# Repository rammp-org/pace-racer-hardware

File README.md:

# PACE Racer motor controller (KiCad hardware)
Welcome to the official hardware repository for the **PACE V0 (RACER)** motor controller board. This repository contains all KiCad design schematics, layout files, and hardware documentation required to manufacture, test, and interface with the RACER platform. 
The companion firmware for this board is under active development in the companion repository: `pace-racer-firmware`.

**How this repo works:** humans commit KiCad sources; CI (KiBot) runs ERC and DRC on every PR and builds gerbers, BOM, position, ibom, PDFs, STEP and renders. Tagging `VnRm` publishes those as a GitHub Release. See `docs/style-guide.md` for conventions and `docs/decisions/` for the why behind unusual choices.
<div align="center">

## Documentation & Resources
### Access the [schematics and an interactive board viewer here!](https://kicanvas.org/?repo=https%3A%2F%2Fgithub.com%2Frammp-org%2Fpace-racer-hardware%2Ftree%2Fmain%2Fpace-core)

---

<div align="left">

## Hardware Architecture Overview

The PACE V0 (RACER) is a high-performance, intelligent 3-phase inverter platform powered by an ESP32-S3. It is engineered to support both high-frequency **Field-Oriented Control (FOC)** and traditional **Trapezoidal (Block) Commutation** strategies. 

``` mermaid
flowchart TD
    %% Upstream USB Environment
    subgraph Upstream ["Upstream Side (Isolated USB Environment)"]
        USB["USB-C Connector<br>(USB1)"] -->|VBUS / GND_USB| VUSB["+5V-USB Rail<br>& GND-USB Rail"]
        VUSB -->|Powers Upstream Side| ISO_In["ADUM3160 Digital Isolator<br>(U4 Upstream Pins)"]
    end

    %% Galvanic Isolation Barrier
    subgraph Barrier ["Galvanic Isolation Boundary"]
        ISO_In -.->|Optical/Magnetic Data Isolation| ISO_Out["ADUM3160 Digital Isolator<br>(U4 Downstream Pins)"]
        SW3{"SW3 Switch<br>(DPDT)"}
    end

    %% High Voltage Input Power Stage
    subgraph HV_Stage ["High-Voltage Input Power Stage"]
        BATT["+BATT Input Rail<br>(48V Nominal Target)"] --> Caps["DC-Link Capacitor Buffers<br>(100V Continuous Rating Limit)"]
        Caps --> XLBuck["XL7015E1 Buck Converter<br>(U6 Stage)"]
    end

    %% Main Logic Subsystems
    subgraph Logic_Rails ["Downstream Logic & Control Subsystem"]
        XLBuck -->|Step Down| V5["+5V Local Rail"]
        
        V5 -->|Linear Regulation| AMS["AMS1117-3.3 LDO (U5)"]
        AMS -->|Logic Power| V33["+3V3 Main MCU Rail"]
        
        V5 -->|Precision Division| REF["REF35160 Reference IC (U7)"]
        REF -->|ADC Baseline Shift| V16["1V6-REF Precision Rail"]
        
        V33 -->|Powers MCU| MCU["ESP32-S3 Processing Core<br>(System GND)"]
        V16 -->|Shunt Offset Bias| MCU
        ISO_Out -->|Isolated USB Signals| MCU
    end

    %% Isolation Mode Controls
    VUSB -->|Route Bus Voltage| SW3
    SW3 -->|Flipped State: Breaks Ground Loops| Logic_Rails
```

### 1. Processing & Inverter Stage
* **Core MCU**: An ESP32-S3-WROOM-1 module handles raw motor control mathematics, wireless telemetry, and hardware interrupt management.
* **Gate Driver**: A TI DRV8353SRTAT 3-phase gate driver provides independent high-side/low-side drive configurations, hardware fault line triggers, and runtime register adjustments via SPI.
* **Power MOSFETs**: 6x ISC0802NLSATMA1 MOSFETs are structured in a traditional 3-phase half-bridge bridge array.
* **Current Sensing**: Dual-purpose inline, low-side 1.0 mΩ current sense shunts (`R1`, `R2`, `R3`) are deployed on all three phases to capture fast current waveforms for precision FOC.

### 2. Sensor Framework
* **Rotor Position Feedback**: Supports dual encoder paradigms:
  * High-speed SPI telemetry via the MT6701 Magnetic Rotary Encoder interface.
  * Discrete input lines for standard 3-phase Hall effect sensor elements (`hall-a`, `hall-b`, `hall-c`).
* **Thermal Management**: 4x LM75ADP I2C digital temperature monitors are distributed across key thermal zones on a single I2C bus. Fixed hardware addressing assigns them respectively to `0x4C`, `0x4D`, `0x4E`, and `0x4F`.

### 3. Communications & Safety
* **Wired Networking**: A Wiznet W5500 Ethernet Coprocessor configuration allows stable, high-throughput network communication over a shared high-speed SPI bus.
* **Galvanic Isolation**: The upstream USB-C debugging connection features an ADUM3160BRWZ-RL digital isolation chip to safely separate logic lines from high-voltage battery transient grounds (see `docs/decisions/0001-ground-domains.md`) during live tuning.

---

## Hardware Pin Mapping Reference

This table is generated from the schematic netlist by `tools/gen_readme.py` and checked in CI. Do not edit it by hand.
Net names follow `docs/style-guide.md` (lowercase domain-kebab); the firmware `hal_pins.h` should use these names.

<!-- BEGIN GENERATED: pinmap -->
| MCU pin | Net | Connected to |
| :-- | :-- | :-- |
| IO0/st-boot (pin 27) | `mcu-boot` | R8, SW1 |
| RXD0 (pin 36) | `uart-rx` | J4 |
| TXD0 (pin 37) | `uart-tx` | J4 |
| IO1/adc1-0 (pin 39) | `vref-1v6` | C23, C27, TP24, U2, U7 |
| IO2/adc1-1 (pin 38) | `mcu-io2` | J4 |
| IO3/st-jtag/adc1-2 (pin 15) | `hall-a` | C42, R34 |
| IO4/adc1-3 (pin 4) | `isense-a` | C30, R10 |
| IO5/adc1-4 (pin 5) | `isense-b` | C29, R21 |
| IO6/adc1-5 (pin 6) | `isense-c` | C28, R22 |
| IO7/adc1-6 (pin 7) | `pwm-c-low` | R26, U2 |
| IO8/adc1-7 (pin 12) | `pwm-a-high` | R31, U2 |
| IO9/adc1-8 (pin 17) | `hall-c` | C40, R25 |
| IO10/adc1-9/FSPI-CS (pin 18) | `eth-spi-cs` | J2, R23 |
| IO11/FSPI-D (pin 19) | `spi-copi` | J2, U2 |
| IO12/FSPI-CLK (pin 20) | `spi-clk` | J2, U2 |
| IO13/FSPI-Q (pin 21) | `spi-cipo` | J2, R17, U2 |
| IO14 (pin 22) | `eth-irq` | J2 |
| IO15 (pin 8) | `pwm-c-high` | R27, U2 |
| IO16 (pin 9) | `pwm-b-low` | R28, U2 |
| IO17 (pin 10) | `pwm-b-high` | R29, U2 |
| IO18 (pin 11) | `pwm-a-low` | R30, U2 |
| IO19/USBD- (pin 13) | `usb-dm` | U4 |
| IO20/USBD+ (pin 14) | `usb-dp` | U4 |
| IO21 (pin 23) | `eth-reset` | J2 |
| IO35 (pin 28) | `enc-spi-cipo` | U12 |
| IO36 (pin 29) | `enc-spi-copi` | J4, U12 |
| IO37 (pin 30) | `enc-spi-clk` | U12 |
| IO38 (pin 31) | `enc-spi-cs` | R24, U12 |
| IO39 (pin 32) | `drv-spi-cs` | U2 |
| IO40 (pin 33) | `drv-fault` | R16, U2 |
| IO41 (pin 34) | `led-green` | D2, J4 |
| IO42 (pin 35) | `led-blue` | D1, J4 |
| IO45/st-spi-v (pin 26) | `i2c-sda` | J4, R39, U10, U11, U8, U9 |
| IO46/st-rom (pin 16) | `hall-b` | C41, R33 |
| IO47 (pin 24) | `drv-enable` | R32, U2 |
| IO48 (pin 25) | `i2c-scl` | J4, R40, U10, U11, U8, U9 |
| EN (pin 3) | `mcu-reset` | R9, SW2 |
<!-- END GENERATED: pinmap -->

---

## Power Distribution & Topology

The RACER PCB layout handles standard heavy industrial current loops alongside sensitive logic rails. Care must be taken during low-level development to understand the distinct ground rules and supply behavior.

* **Main DC Power Stage Input (`+BATT`)**: Accepts high-voltage input up to 60V DC. High and low-frequency buffer capacitor banks are placed immediately across each half-bridge phase to suppress heavy inductive switching ripples up to 25MHz.
* **Logic Subsystem Buck (5V Rail)**: Driven by an XL7015E1 high-voltage buck regulator topology, dropping the high-voltage input down to a common local 5V line.
* **Microcontroller Supply (3.3V Rail)**: An AMS1117-3.3 linear regulator drops the local 5V line to a stable 3.3V rail dedicated to powering the ESP32-S3 and onboard sensors.
* **Analog Ingestion Bias Reference (`vref-1v6`)**: Formed via a REF35160QDBVR high-precision reference generator connected to the 5V line. This outputs a fixed 1.6V reference bias to calibrate the inline current shunt amplifiers, permitting measurement of negative and positive phase currents across the full bi-directional stroke.
* **Isolation Boundary Notice**: The 5V-USB rail is strictly limited to powering the upstream digital isolator components. Flipping the physical isolation switch (`SW3`) cleanly detaches the target ground (`GND`) from development computer USB shields (`GND-USB`) to protect computer infrastructure against high-power faults.

---

## First-Stage Firmware Initialization Blueprint

To quickly bring up prototype firmware on `pace-racer-firmware`, organize your driver initializations using this execution checklist:

### Phase 1: Core Systems & Diagnostic Telemetry
1. Define the physical I/O allocations outlined in the pin reference table.
2. Initialize diagnostic LEDs (`IO41`, `IO42`) to indicate a booting state.
3. Fire up the shared I2C bus over `IO45` and `IO48` to loop and register responses from the four LM75ADP temperature sensor configurations at addresses `0x4C` through `0x4F`. 

### Phase 2: Inverter Protection & Commutation Interfaces
1. Configure `IO40` (`drv-fault`) as an active-low hardware interrupt line. Ensure its handler instantly forces all PWM generation lines into a low (disabled) safety state if triggered.
2. Initialize the main SPI communications bus over pins `spi-copi`, `spi-clk`, and `spi-cipo`. Pull the gate driver chip select (`IO39`) low to configure the DRV8353 operational state registers.
3. For **Field-Oriented Control (FOC)**, configure high-speed SPI capture over the encoder subsystem (`IO35`, `IO37`, `IO38`) to decode magnetic orientation data from the MT6701.
4. For **Trapezoidal Commutation**, establish change-of-state interrupt routines tracking discrete pin changes across Hall effect inputs (`IO3`, `IO46`, `IO9`).

### Phase 3: Ethernet Networking
1. Cycle the hardware reset pin `IO21` to clear the internal registers of the W5500 Ethernet chip.
2. Configure SPI tracking over the controller chip select pin `IO10`.
3. Initialize the raw sockets over network stacks using the standard `eth-irq` (`IO14`) interrupt pin to manage incoming and outgoing network interface events without blocking the high-frequency motor control loops.

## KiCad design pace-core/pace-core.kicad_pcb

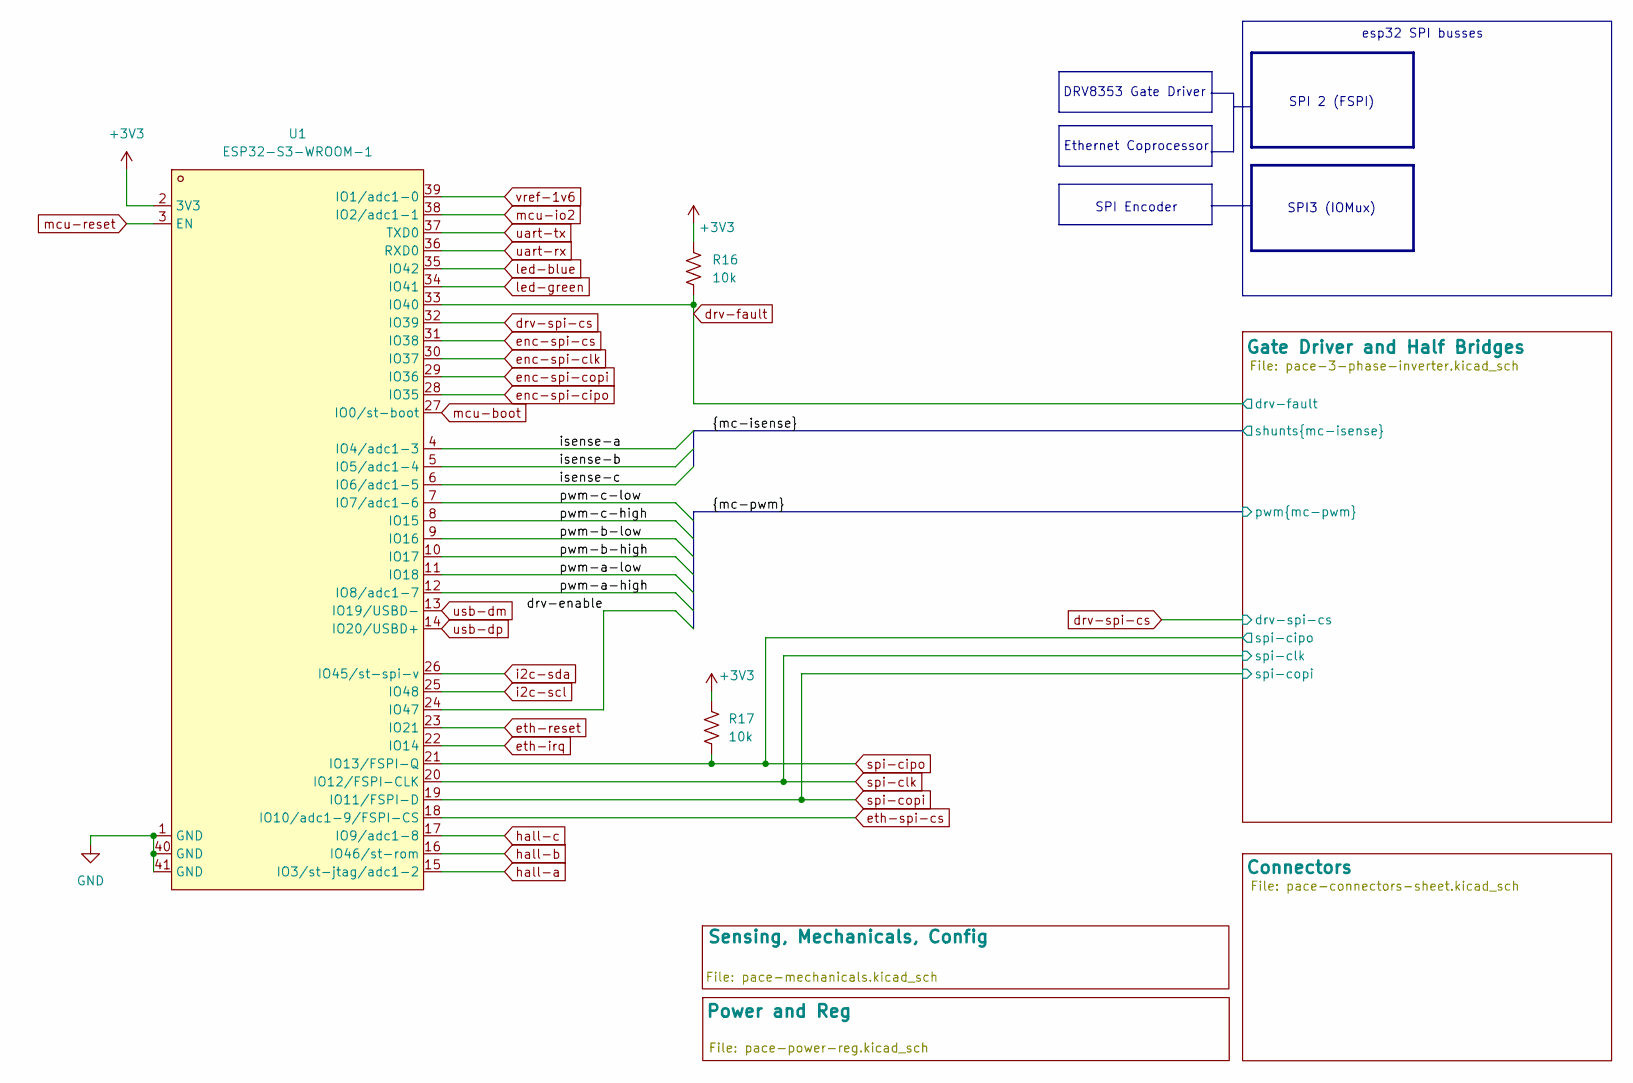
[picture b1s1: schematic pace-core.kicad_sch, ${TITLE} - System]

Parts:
R16, R17: 10k; R_0402_1005Metric
U1: ESP32-S3-WROOM-1; WIRELM-SMD_ESP32-S3-WROOM-1; MPN ESP32-S3-WROOM-1-N16R2; LCSC Part C2913205

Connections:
+3V3: R16.1, R17.1, U1.2 (3V3); also elsewhere on the board
/drv-enable: U1.24 (IO47); also elsewhere on the board
/isense-a: U1.4 (IO4/adc1-3); also elsewhere on the board
/isense-b: U1.5 (IO5/adc1-4); also elsewhere on the board
/isense-c: U1.6 (IO6/adc1-5); also elsewhere on the board
/pwm-a-high: U1.12 (IO8/adc1-7); also elsewhere on the board
/pwm-a-low: U1.11 (IO18); also elsewhere on the board
/pwm-b-high: U1.10 (IO17); also elsewhere on the board
/pwm-b-low: U1.9 (IO16); also elsewhere on the board
/pwm-c-high: U1.8 (IO15); also elsewhere on the board
/pwm-c-low: U1.7 (IO7/adc1-6); also elsewhere on the board
GND: U1.1 (GND), U1.40 (GND), U1.41 (GND); also elsewhere on the board
drv-fault: R16.2, U1.33 (IO40); also elsewhere on the board
drv-spi-cs: U1.32 (IO39); also elsewhere on the board
enc-spi-cipo: U1.28 (IO35); also elsewhere on the board
enc-spi-clk: U1.30 (IO37); also elsewhere on the board
enc-spi-copi: U1.29 (IO36); also elsewhere on the board
enc-spi-cs: U1.31 (IO38); also elsewhere on the board
eth-irq: U1.22 (IO14); also elsewhere on the board
eth-reset: U1.23 (IO21); also elsewhere on the board
eth-spi-cs: U1.18 (IO10/adc1-9/FSPI-CS); also elsewhere on the board
hall-a: U1.15 (IO3/st-jtag/adc1-2); also elsewhere on the board
hall-b: U1.16 (IO46/st-rom); also elsewhere on the board
hall-c: U1.17 (IO9/adc1-8); also elsewhere on the board
i2c-scl: U1.25 (IO48); also elsewhere on the board
i2c-sda: U1.26 (IO45/st-spi-v); also elsewhere on the board
led-blue: U1.35 (IO42); also elsewhere on the board
led-green: U1.34 (IO41); also elsewhere on the board
mcu-boot: U1.27 (IO0/st-boot); also elsewhere on the board
mcu-io2: U1.38 (IO2/adc1-1); also elsewhere on the board
mcu-reset: U1.3 (EN); also elsewhere on the board
spi-cipo: R17.2, U1.21 (IO13/FSPI-Q); also elsewhere on the board
spi-clk: U1.20 (IO12/FSPI-CLK); also elsewhere on the board
spi-copi: U1.19 (IO11/FSPI-D); also elsewhere on the board
uart-rx: U1.36 (RXD0); also elsewhere on the board
uart-tx: U1.37 (TXD0); also elsewhere on the board
usb-dm: U1.13 (IO19/USBD-); also elsewhere on the board
usb-dp: U1.14 (IO20/USBD+); also elsewhere on the board

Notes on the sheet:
SPI3 (IOMux)
SPI 2 (FSPI)
SPI Encoder
Ethernet Coprocessor
DRV8353 Gate Driver
esp32 SPI busses

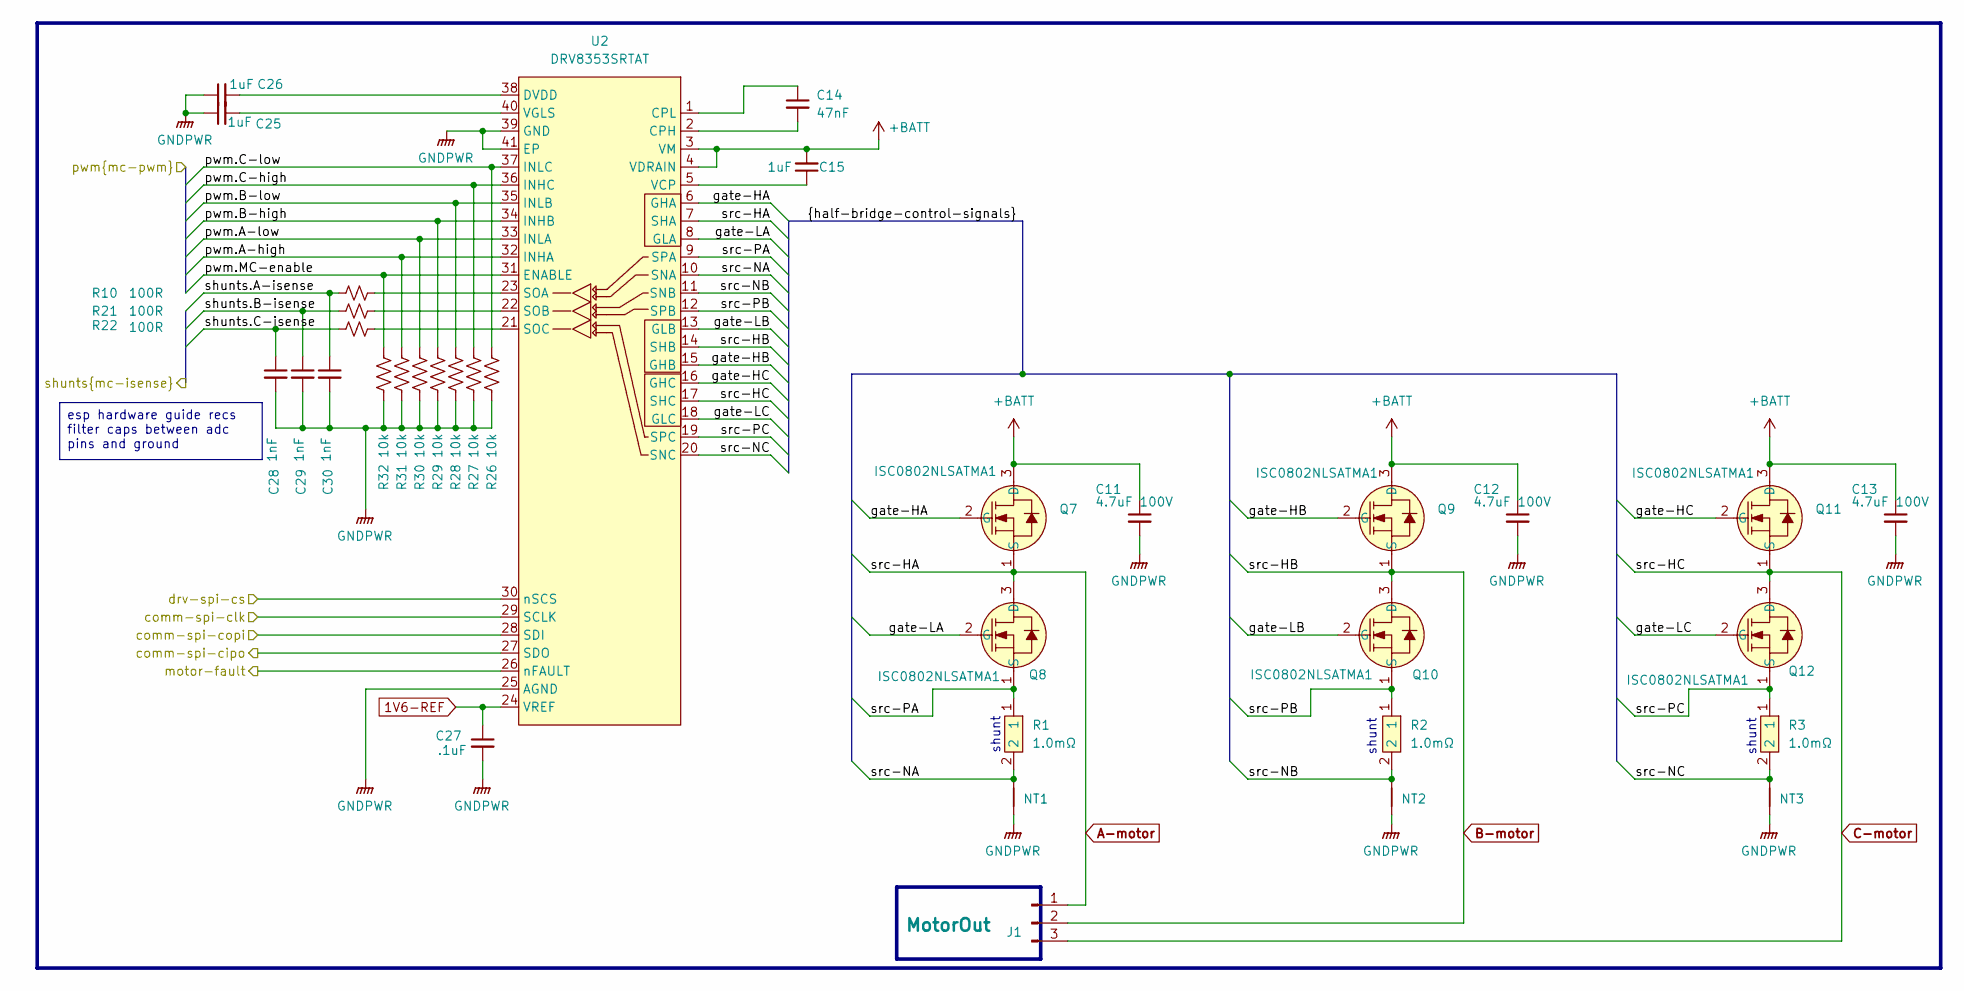
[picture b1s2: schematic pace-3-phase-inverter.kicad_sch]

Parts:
C11, C12, C13: 4.7uF 100V; C_1210_3225Metric
C14: 47nF; C_0603_1608Metric
C15, C25, C26: 1uF; C_1206_3216Metric
C27: .1uF; C_0402_1005Metric
C28, C29, C30: 1nF; C_0402_1005Metric
J1: MotorOut; 3PhaseMotorPigtail
NT1, NT2, NT3: NetTie_2; shunt-net-tie
Q7, Q8, Q9, Q10, Q11, Q12: ISC0802NLSATMA1; PG-TDSON-8_L5.9-W5.1-P1.27-LS6.1-BL; MPN ISC0802NLSATMA1; LCSC Part C3288904
R1, R2, R3: 1.0mΩ; RES-SMD_L6.3-W3.1-1; MPN DSLR-M-3-1F; LCSC Part C41382682
R10, R21, R22: 100R; R_0402_1005Metric
R26, R27, R28, R29, R30, R31, R32: 10k; R_0402_1005Metric
U2: DRV8353SRTAT; WQFN-40_L6.0-W6.0-P0.50-TL-EP4.2; MPN DRV8353SRTAT; LCSC Part C2150480

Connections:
+BATT: C11.1, C12.1, C13.1, C15.2, Q7.3 (D), Q9.3 (D), Q11.3 (D), U2.3 (VM), U2.4 (VDRAIN); also elsewhere on the board
/Gate Driver and Half Bridges/gate-a-high: Q7.2 (G), U2.6 (GHA)
/Gate Driver and Half Bridges/gate-a-low: Q8.2 (G), U2.8 (GLA)
/Gate Driver and Half Bridges/gate-b-high: Q9.2 (G), U2.15 (GHB)
/Gate Driver and Half Bridges/gate-b-low: Q10.2 (G), U2.13 (GLB)
/Gate Driver and Half Bridges/gate-c-high: Q11.2 (G), U2.16 (GHC)
/Gate Driver and Half Bridges/gate-c-low: Q12.2 (G), U2.18 (GLC)
/Gate Driver and Half Bridges/shunt-a-n: NT1.2, R1.2, U2.10 (SNA)
/Gate Driver and Half Bridges/shunt-a-p: Q8.1 (S), R1.1, U2.9 (SPA)
/Gate Driver and Half Bridges/shunt-b-n: NT2.2, R2.2, U2.11 (SNB)
/Gate Driver and Half Bridges/shunt-b-p: Q10.1 (S), R2.1, U2.12 (SPB)
/Gate Driver and Half Bridges/shunt-c-n: NT3.2, R3.2, U2.20 (SNC)
/Gate Driver and Half Bridges/shunt-c-p: Q12.1 (S), R3.1, U2.19 (SPC)
/drv-enable: R32.2, U2.31 (ENABLE); also elsewhere on the board
/isense-a: C30.1, R10.1; also elsewhere on the board
/isense-b: C29.1, R21.1; also elsewhere on the board
/isense-c: C28.1, R22.1; also elsewhere on the board
/pwm-a-high: R31.2, U2.32 (INHA); also elsewhere on the board
/pwm-a-low: R30.2, U2.33 (INLA); also elsewhere on the board
/pwm-b-high: R29.2, U2.34 (INHB); also elsewhere on the board
/pwm-b-low: R28.2, U2.35 (INLB); also elsewhere on the board
/pwm-c-high: R27.2, U2.36 (INHC); also elsewhere on the board
/pwm-c-low: R26.2, U2.37 (INLC); also elsewhere on the board
GND: C11.2, C12.2, C13.2, C25.1, C26.1, C27.2, C28.2, C29.2, C30.2, NT1.1, NT2.1, NT3.1, R26.1, R27.1, R28.1, R29.1, R30.1, R31.1, R32.1, U2.25 (AGND), U2.39 (GND), U2.41 (EP); also elsewhere on the board
unnamed: C14.2, U2.2 (CPH)
unnamed: C14.1, U2.1 (CPL)
unnamed: C26.2, U2.38 (DVDD)
unnamed: R10.2, U2.23 (SOA)
unnamed: R21.2, U2.22 (SOB)
unnamed: R22.2, U2.21 (SOC)
unnamed: C15.1, U2.5 (VCP)
unnamed: C25.2, U2.40 (VGLS)
drv-fault: U2.26 (nFAULT); also elsewhere on the board
drv-spi-cs: U2.30 (nSCS); also elsewhere on the board
mot-a: J1.1, Q7.1 (S), Q8.3 (D), U2.7 (SHA)
mot-b: J1.2, Q9.1 (S), Q10.3 (D), U2.14 (SHB)
mot-c: J1.3, Q11.1 (S), Q12.3 (D), U2.17 (SHC)
spi-cipo: U2.27 (SDO); also elsewhere on the board
spi-clk: U2.29 (SCLK); also elsewhere on the board
spi-copi: U2.28 (SDI); also elsewhere on the board

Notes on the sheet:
shunt
esp hardware guide recs filter caps between adc pins and ground

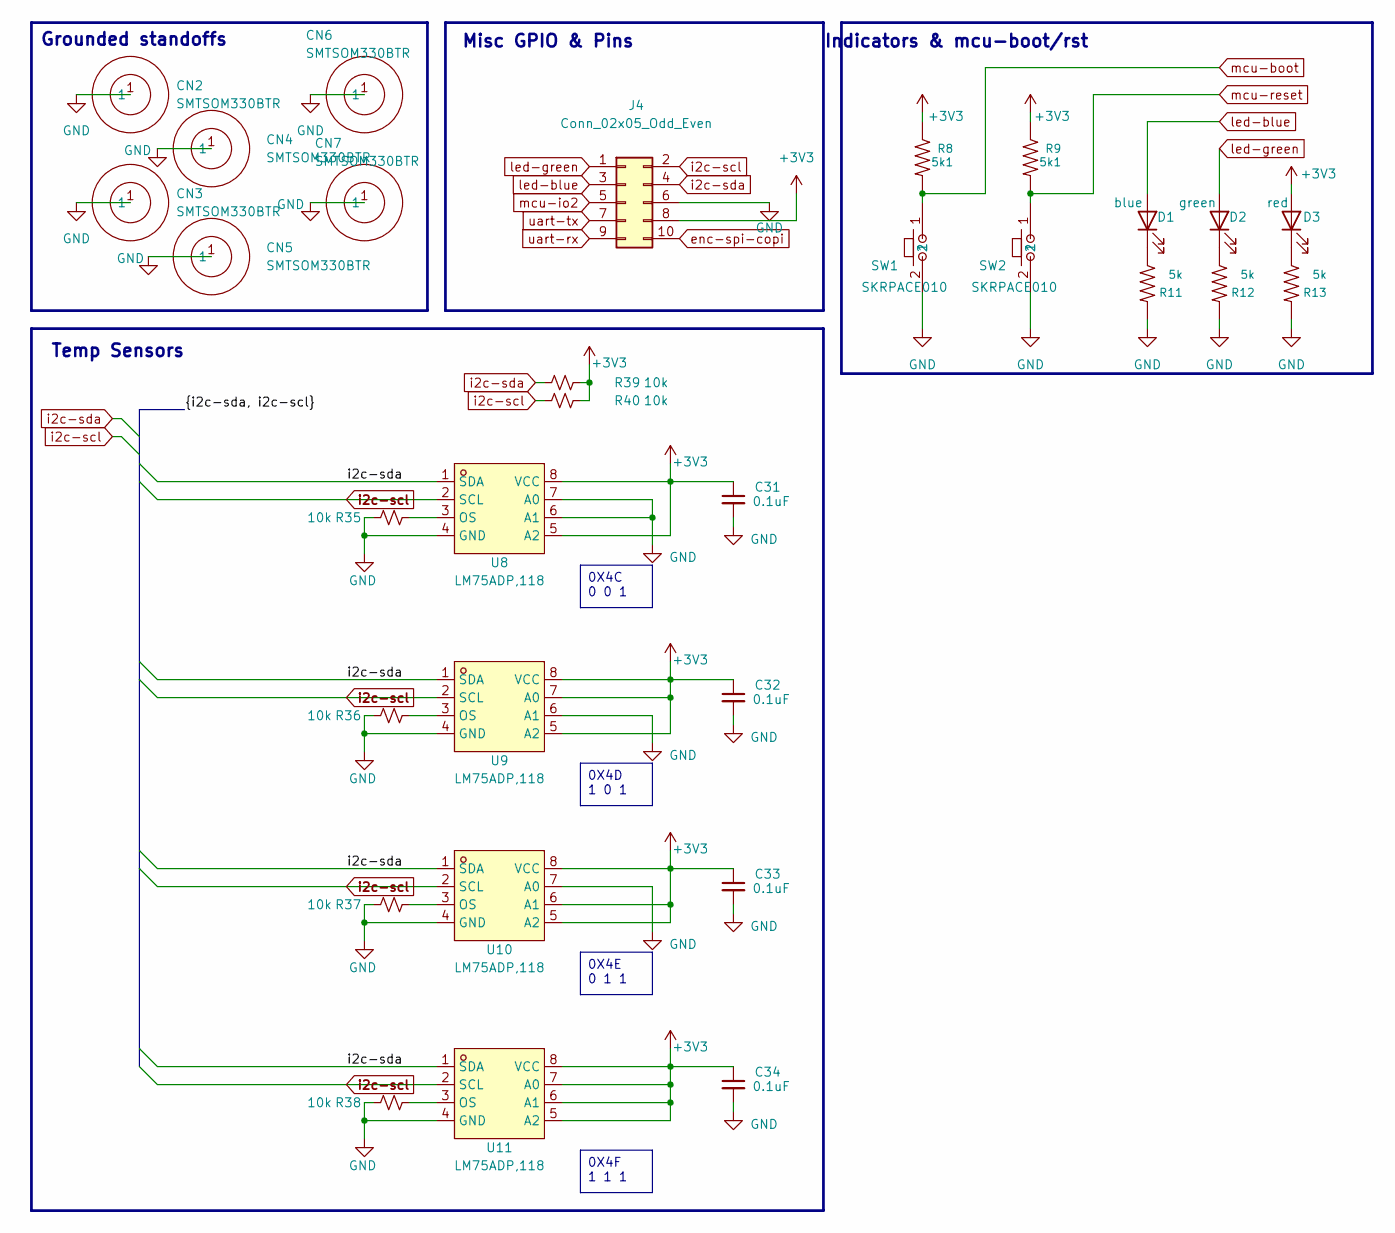
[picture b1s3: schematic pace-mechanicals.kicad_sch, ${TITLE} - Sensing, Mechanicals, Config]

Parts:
C31, C32, C33, C34: 0.1uF; C_0402_1005Metric
CN2, CN3, CN4, CN5, CN6, CN7: SMTSOM330BTR; M3-TH_BD6.0-D4.3; MPN SMTSOM330BTR; LCSC Part C5221843
D1: blue; LED_0805_2012Metric; LCSC_Part_Number C84259
D2: green; LED_0805_2012Metric; LCSC_Part_Number C84260
D3: red; LED_0805_2012Metric; LCSC_Part_Number C84256
J4: Conn_02x05_Odd_Even; PinHeader_2x05_P2.54mm_Vertical_SMD
R8, R9: 5k1; R_0402_1005Metric; LCSC_Part_Number C25905
R11, R12, R13: 5k; R_0402_1005Metric; LCSC_Part_Number C11702
R35, R36, R37, R38, R39, R40: 10k; R_0402_1005Metric
SW1, SW2: SKRPACE010; KEY-SMD_4P-L4.2-W3.2-P2.20-LS4.6; MPN SKRPACE010; LCSC Part C139797
U8, U9, U10, U11: LM75ADP,118; TSSOP-8_L3.0-W3.0-P0.65-LS4.9-BL; MPN LM75ADP,118; LCSC Part C843694

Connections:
+3V3: C31.1, C32.1, C33.1, C34.1, D3.2 (A), J4.8, R8.1, R9.1, R39.2, R40.2, U8.5 (A2), U8.8 (VCC), U9.5 (A2), U9.7 (A0), U9.8 (VCC), U10.5 (A2), U10.6 (A1), U10.8 (VCC), U11.5 (A2), U11.6 (A1), U11.7 (A0), U11.8 (VCC); also elsewhere on the board
GND: C31.2, C32.2, C33.2, C34.2, CN2.1 (1_1), CN3.1 (1_1), CN4.1 (1_1), CN5.1 (1_1), CN6.1 (1_1), CN7.1 (1_1), J4.6, R11.2, R12.2, R13.2, R35.2, R36.2, R37.2, R38.2, SW1.2, SW2.2, U8.4 (GND), U8.6 (A1), U8.7 (A0), U9.4 (GND), U9.6 (A1), U10.4 (GND), U10.7 (A0), U11.4 (GND); also elsewhere on the board
unnamed: D1.1 (K), R11.1
unnamed: D2.1 (K), R12.1
unnamed: D3.1 (K), R13.1
unnamed: R35.1, U8.3 (OS)
unnamed: R36.1, U9.3 (OS)
unnamed: R37.1, U10.3 (OS)
unnamed: R38.1, U11.3 (OS)
enc-spi-copi: J4.10; also elsewhere on the board
i2c-scl: J4.2, R40.1, U8.2 (SCL), U9.2 (SCL), U10.2 (SCL), U11.2 (SCL); also elsewhere on the board
i2c-sda: J4.4, R39.1, U8.1 (SDA), U9.1 (SDA), U10.1 (SDA), U11.1 (SDA); also elsewhere on the board
led-blue: D1.2 (A), J4.3; also elsewhere on the board
led-green: D2.2 (A), J4.1; also elsewhere on the board
mcu-boot: R8.2, SW1.1; also elsewhere on the board
mcu-io2: J4.5; also elsewhere on the board
mcu-reset: R9.2, SW2.1; also elsewhere on the board
uart-rx: J4.9; also elsewhere on the board
uart-tx: J4.7; also elsewhere on the board

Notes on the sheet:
Temp Sensors
Indicators & mcu-boot/rst
Misc GPIO & Pins
Grounded standoffs
0X4D 1 0 1
0X4E 0 1 1
0X4C 0 0 1
0X4F 1 1 1

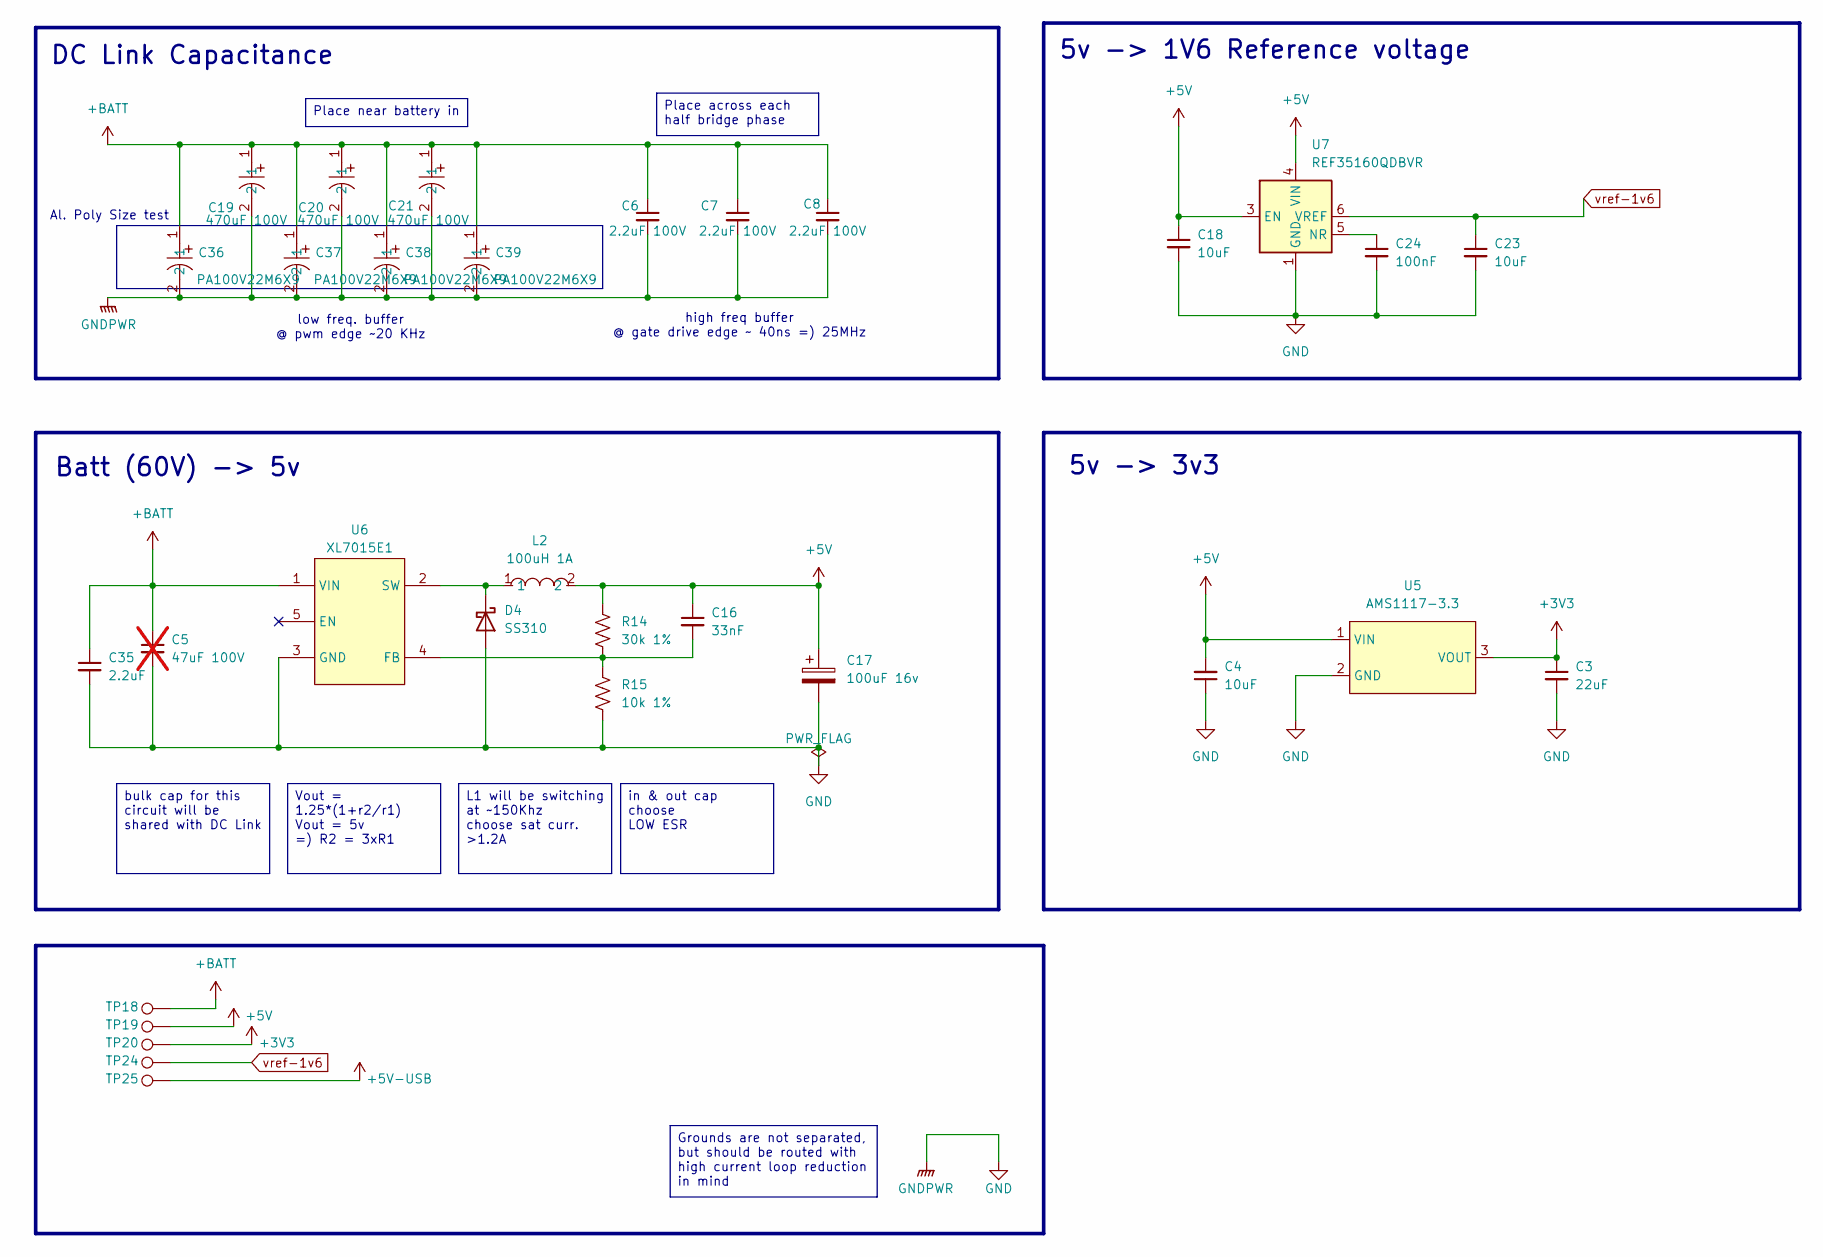
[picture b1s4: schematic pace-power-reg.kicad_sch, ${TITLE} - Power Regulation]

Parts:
C3: 22uF; C_0603_1608Metric
C4, C18, C23: 10uF; C_0603_1608Metric
C5: 47uF 100V; not fitted
C6, C7, C8: 2.2uF 100V; C_1206_3216Metric
C16: 33nF; C_0402_1005Metric
C17: 100uF 16v; C_Elec_6.3x7.7; MPN EEEFPV101XAP; LCSC Part C178585
C19, C20, C21: 470uF 100V; CAP-TH_BD16.0-P7.50-D1.2-FD; MPN NXH100VB470M16*31.5 LO; LCSC Part C18164658
C24: 100nF; C_0402_1005Metric
C35: 2.2uF; C_1210_3225Metric
C36, C37, C38, C39: PA100V22M6X9; CAP-TH_BD6.3-P2.50-D0.6-FD; MPN PA100V22M6X9; LCSC Part C49233038
D4: SS310; D_SMA; MPN SS310
L2: 100uH 1A; IND-SMD_L10.0-W10.0_SRU1038-100Y; MPN SRU1038-101Y; LCSC Part C6684389
R14: 30k 1%; R_0402_1005Metric
R15: 10k 1%; R_0402_1005Metric
TP18, TP19, TP20, TP24, TP25: TestPoint; TestPoint_Pad_D2.0mm
U5: AMS1117-3.3; SOT-223-3_L6.5-W3.4-P2.30-LS7.0-BR; MPN AMS1117-3.3; LCSC Part C6186
U6: XL7015E1; TO-252-5_L6.6-W5.8-P1.27-TL; MPN XL7015E1; LCSC Part C73013
U7: REF35160QDBVR; SOT-23-6; MPN REF35160QDBVR

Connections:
+3V3: C3.1, TP20.1 (1_1), U5.3 (VOUT); also elsewhere on the board
+5V: C4.2, C16.1, C17.1, C18.1, L2.2, R14.1, TP19.1 (1_1), U5.1 (VIN), U7.3 (EN), U7.4 (VIN); also elsewhere on the board
+5V-USB: TP25.1 (1_1); also elsewhere on the board
+BATT: C5.1, C6.1, C7.1, C8.1, C19.1, C20.1, C21.1, C35.1, C36.1, C37.1, C38.1, C39.1, TP18.1 (1_1), U6.1 (VIN); also elsewhere on the board
GND: C3.2, C4.1, C5.2, C6.2, C7.2, C8.2, C17.2, C18.2, C19.2, C20.2, C21.2, C23.2, C24.2, C35.2, C36.2, C37.2, C38.2, C39.2, D4.2 (A), R15.2, U5.2 (GND), U6.3 (GND), U7.1 (GND), U7.2 (GND); also elsewhere on the board
unnamed: D4.1 (K), L2.1, U6.2 (SW)
unnamed: C16.2, R14.2, R15.1, U6.4 (FB)
unnamed: C24.1, U7.5 (NR)

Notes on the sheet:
5v -> 1V6 Reference voltage
high freq buffer @ gate drive edge ~ 40ns =) 25MHz
5v -> 3v3
Batt (60V) -> 5v
low freq. buffer @ pwm edge ~20 KHz
DC Link Capacitance
Al. Poly Size test
Place across each half bridge phase
Place near battery in
Grounds are not separated, but should be routed with high current loop reduction in mind
Vout = 1.25*(1+r2/r1) Vout = 5v =) R2 = 3xR1
in & out cap choose LOW ESR
L1 will be switching at ~150Khz choose sat curr. >1.2A
bulk cap for this circuit will be shared with DC Link

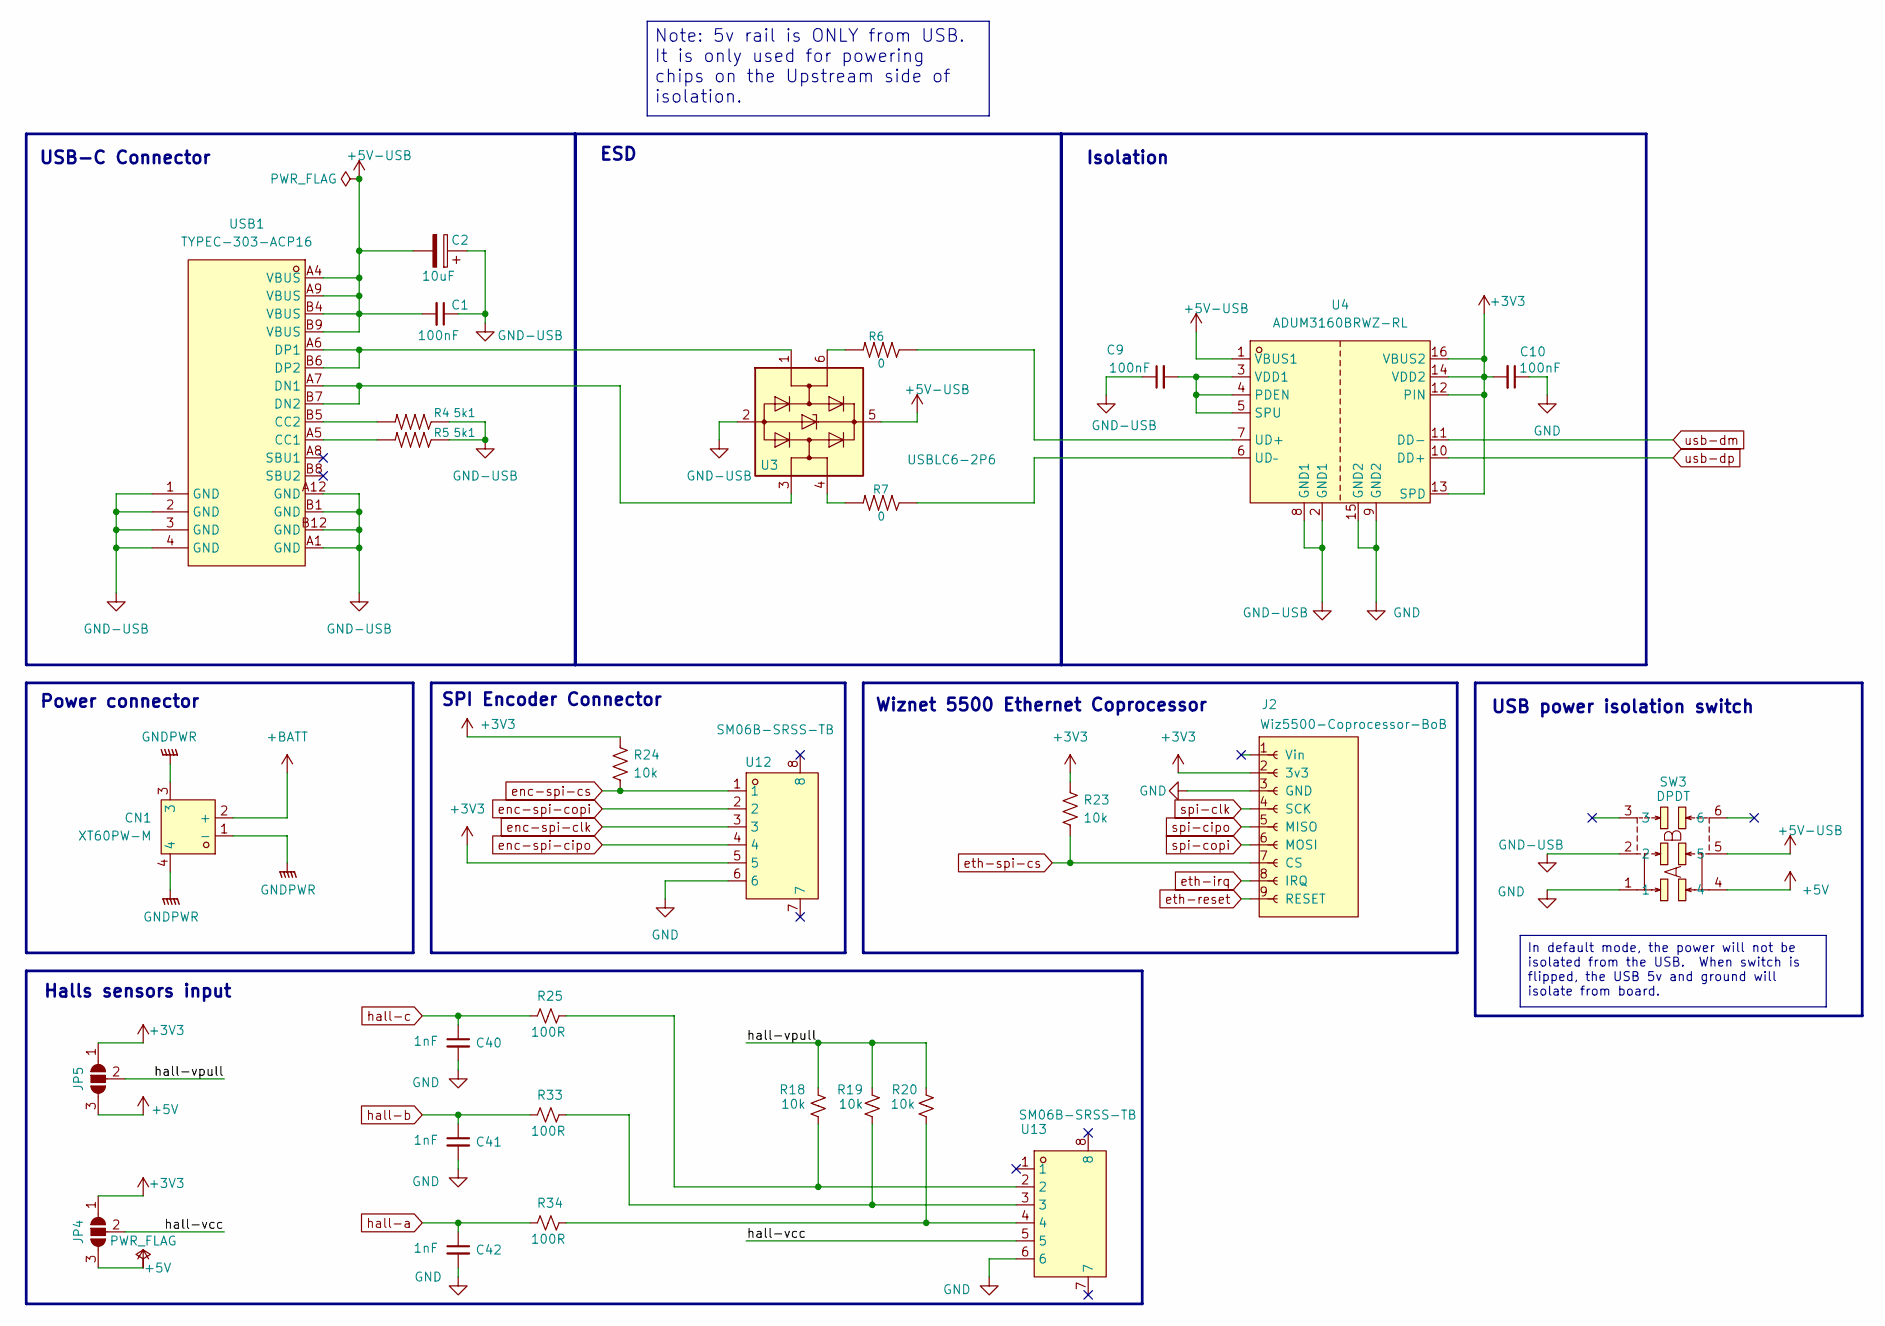
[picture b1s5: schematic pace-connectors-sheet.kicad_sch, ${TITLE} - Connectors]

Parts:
C1, C9, C10: 100nF; C_0603_1608Metric
C2: 10uF; C_1206_3216Metric
C40, C41, C42: 1nF; C_0402_1005Metric
CN1: XT60PW-M; CONN-TH_XT60PW-M; MPN XT60PW-M; LCSC Part C98732
J2: Wiz5500-Coprocessor-BoB; PinSocket_1x09_P2.54mm_Vertical_SMD_Pin1Left
JP4, JP5: SolderJumper_3_Bridged12; SolderJumper-3_P1.3mm_Open_RoundedPad1.0x1.5mm
R4, R5: 5k1; R_0402_1005Metric; LCSC_Part_Number C25905
R6, R7: 0; R_0402_1005Metric; LCSC_Part_Number C3017451
R18, R19, R20, R23, R24: 10k; R_0402_1005Metric
R25, R33, R34: 100R; R_0402_1005Metric
SW3: DPDT; SW-SMD_MST22D18G2; MPN MST22D18G2 125; LCSC Part C2906280
U3: USBLC6-2P6; SOT-666; MPN USBLC6-2P6; LCSC_Part_Number C2827693
U4: ADUM3160BRWZ-RL; SOIC-16_L10.3-W7.5-P1.27-LS10.3-BL; MPN ADUM3160BRWZ-RL; LCSC Part C284149
U12, U13: SM06B-SRSS-TB; CONN-SMD_SM06B-SRSS-TB-LF-SN; MPN SM06B-SRSS-TB(LF)(SN); LCSC Part C160405
USB1: TYPEC-303-ACP16; USB-C-SMD_TYPEC-303-ACP16; MPN TYPEC-303-ACP16; LCSC Part C720628

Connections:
+3V3: C10.2, J2.2 (3v3), JP4.1 (A), JP5.1 (A), R23.1, R24.1, U4.12 (PIN), U4.13 (SPD), U4.14 (VDD2), U4.16 (VBUS2), U12.5; also elsewhere on the board
+5V: JP4.3 (B), JP5.3 (B), SW3.4; also elsewhere on the board
+5V-USB: C1.2, C2.2, SW3.5, U3.5 (VBUS), U4.1 (VBUS1), USB1.A4 (VBUS), USB1.A9 (VBUS), USB1.B4 (VBUS), USB1.B9 (VBUS); also elsewhere on the board
+BATT: CN1.2 (+); also elsewhere on the board
/Connectors/hall-vcc: JP4.2 (C), U13.5
/Connectors/hall-vpull: JP5.2 (C), R18.2, R19.2, R20.2
GND: C10.1, C40.2, C41.2, C42.2, CN1.1 (-), CN1.3, CN1.4, J2.3 (GND), SW3.1, U4.9 (GND2), U4.15 (GND2), U12.6, U13.6; also elsewhere on the board
GND-USB: C1.1, C2.1, C9.1, R4.1, R5.1, SW3.2, U3.2 (GND), U4.2 (GND1), U4.8 (GND1), USB1.1 (GND), USB1.2 (GND), USB1.3 (GND), USB1.4 (GND), USB1.A1 (GND), USB1.A12 (GND), USB1.B1 (GND), USB1.B12 (GND)
unnamed: R6.2, U3.6 (I/O1)
unnamed: R7.2, U3.4 (I/O2)
unnamed: R18.1, R25.2, U13.2
unnamed: R19.1, R33.2, U13.3
unnamed: R20.1, R34.2, U13.4
unnamed: C9.2, U4.3 (VDD1), U4.4 (PDEN), U4.5 (SPU)
unnamed: R6.1, U4.7 (UD+)
unnamed: R7.1, U4.6 (UD–)
unnamed: R5.2, USB1.A5 (CC1)
unnamed: R4.2, USB1.B5 (CC2)
unnamed: U3.3 (I/O2), USB1.A7 (DN1), USB1.B7 (DN2)
unnamed: U3.1 (I/O1), USB1.A6 (DP1), USB1.B6 (DP2)
enc-spi-cipo: U12.4; also elsewhere on the board
enc-spi-clk: U12.3; also elsewhere on the board
enc-spi-copi: U12.2; also elsewhere on the board
enc-spi-cs: R24.2, U12.1; also elsewhere on the board
eth-irq: J2.8 (IRQ); also elsewhere on the board
eth-reset: J2.9 (RESET); also elsewhere on the board
eth-spi-cs: J2.7 (CS), R23.2; also elsewhere on the board
hall-a: C42.1, R34.1; also elsewhere on the board
hall-b: C41.1, R33.1; also elsewhere on the board
hall-c: C40.1, R25.1; also elsewhere on the board
spi-cipo: J2.5 (MISO); also elsewhere on the board
spi-clk: J2.4 (SCK); also elsewhere on the board
spi-copi: J2.6 (MOSI); also elsewhere on the board
usb-dm: U4.11 (DD-); also elsewhere on the board
usb-dp: U4.10 (DD+); also elsewhere on the board

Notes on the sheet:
Wiznet 5500 Ethernet Coprocessor
Power connector
USB power isolation switch
Halls sensors input
Isolation
USB-C Connector
SPI Encoder Connector
ESD
Note: 5v rail is ONLY from USB. It is only used for powering chips on the Upstream side of isolation.
In default mode, the power will not be isolated from the USB. When switch is flipped, the USB 5v and ground will isolate from board.

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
